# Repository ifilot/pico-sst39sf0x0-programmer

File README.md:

# PICO-SST39SF0x0 Programmer

> [!NOTE]  
> Wish to buy an assembled device? Feel free to contact me at ivo@ivofilot.nl. Price will be around €20,00. Will ship from the Netherlands.

> [!TIP]
> There also exists [a command-line tool](https://github.com/ifilot/pico-flasher-cli) to interface with the PICO-SST39SF0x0 Programmer.

> [!CAUTION]  
> Whenever possible, avoid using USB hubs to connect your **PICO-SST39SF0x0 Programmer**. 
> USB hubs can sometimes cause instability in the serial connection, which may 
> lead to crashes or unexpected program behavior.

## Obtaining pre-built binaries

Download the latest version of the binaries via the links below.

* [Firmware PICO (.uf2 file)](https://github.com/ifilot/pico-sst39sf0x0-programmer/releases/latest/download/pico-sst39sf0x0-programmer-firmware.uf2)
* [Firmware PICO2 (.uf2 file)](https://github.com/ifilot/pico-sst39sf0x0-programmer/releases/latest/download/pico2-sst39sf0x0-programmer-firmware.uf2)
* [GUI Installer](https://github.com/ifilot/pico-sst39sf0x0-programmer/releases/latest/download/pico-sst39sf0x0-programmer-installer-win64.exe)

## Purpose

This open hardware project aims users to produce a low-cost flasher for the
[SST39SF0x0 type](https://ww1.microchip.com/downloads/en/DeviceDoc/20005022C.pdf) 
of ROM chips. The flasher revolves around the cheap
[Raspberry PICO](https://www.raspberrypi.com/products/raspberry-pi-pico/) device.

Besides general read/write/erase functionality for the SST39SF0x0 type of ROM
chips, the software and tools delivered with the PICO-SST39SF0x0 Programmer tend
to cater to a number of projects involving the venerable 
[P2000T and P2000M](https://en.wikipedia.org/wiki/Philips_P2000), both early 
Philips home computers of the 1980s. See the list below for the projects that
use the PICO-SST39SF0x0 Programmer flasher.

* [P2000T Cartridges](https://github.com/ifilot/p2000t-cartridges): A set of
  homebrew cartridges designed for the P2000T. These cartridges all use
  SST39SF0x0 type of ROM chips.
* C64 Multirom

Nevertheless, this is a general purpose product and you are able to flash and
kind of data onto the ROM chips.

> [!TIP]  
> If you do not like seeing these ROM files being displayed, you can hide them
> via `Edit > Settings`.

## Device

The fully assembled device will look as seen in the image below. A ZIF-style
socket is used to insert the SST39SF0x0 chip. A reset button button is exposed
which will reset the device. The green and red LEDs will be on during read and
write operations, respectively. At the top-right part of the device, an access
hole is made to insert a long thin wire to press on the `bootsel` button of the
Raspberry Pi PICO. When this button is pressed down and a USB cable is inserted,
the PICO will expose a file system allowing the user to upload the firmware
to the device.

Inside the enclosure is a single PCB that hosts the PICO, the ZIF cartridge
and a number of chips. Since the GPIO pins on the PICO are 3.3V, extensive use
of level shifters is made to hook up the PICO to the SST39SF0x0 chip, whose
pins operate at the 5V logic level. To set the address on the SST39SF0x0 chip,
three 74HC573 chips are being used (U2-U4). A diode (D1) acts as the reverse
polarity protection in the event the user would place the chip in the wrong
direction.

PCB frontside | PCB backside
------------- | ------------
 | 

## GUI

To interface with the device, a GUI is written using the 
[Qt framework](https://www.qt.io/). The GUI scans for all USB devices connected
to the computer with a hardware signature matching the Raspberry Pi PICO. Upon
a match, it tries to access the device. Interfacing with the device occurs via
a [serial communication (COM) port](https://en.wikipedia.org/wiki/COM_(hardware_interface)).
By means of a number of [simple 8-byte command words](firmware/README.md),
instructions can be sent to the device and the corresponding response can be
received. One is not restricted to using the GUI to interface with the device.
An [example set of Python scripts](firmware/scripts) is provided to provide 
an alternative way to communicate with the PICO programmer.

> [!NOTE]  
> There is also a command-line tool available via
> [this repository](https://github.com/ifilot/pico-flasher-cli).

## Documentation and tutorials

A number of useful tutorials to work with the PICO programmer are provided
below.

* [Flashing the device / updating firmware](https://www.philips-p2000t.nl/tools/pico-sst39sf0x0-programmer.html#flashing-firmware-to-the-programmer)
* [Using the programmer to create copies of P2000T cartridges](https://www.philips-p2000t.nl/tools/pico-sst39sf0x0-programmer-slot1-adapter-board.html)
* [Using the PICO programmer in combination with the P2000T ZIF-cartridge](https://www.philips-p2000t.nl/cartridges/zif-cartridge.html#zif-cartridge)

## Schematics

[Download schematics as PDF](pcb/pico-sst39sf0x0-pcb/pico-sst39sf0x0-pcb.pdf)

## Contents

* [Case](case): Set of .stl files to print a handy case for your flash device.
* [Firmware](firmware): Firmware for your PICO to interface with the GUI.
* [GUI](gui): Qt-based GUI to interface with your PICO.
* [PCB](pcb): Kicad files to produce the PICO flash device and the PLCC32 adapter board.
* [Scripts](scripts): Number of Python scripts the correct working of your PICO
  device.

## License

* All software is shared under the [GPL v3 license](https://www.gnu.org/licenses/gpl-3.0).
* All hardware (e.g. KiCAD files and .stl files) are shared under the [CC-BY-SA 4.0 license](https://creativecommons.org/licenses/by-sa/4.0/).

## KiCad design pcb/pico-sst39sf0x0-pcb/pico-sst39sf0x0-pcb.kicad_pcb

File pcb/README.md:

# PCBs

This folder contains three subfolders containing the KiCAD files for three
PCBs

* [pico-sst39sf0x0-pcb](pico-sst39sf0x0-pcb): Core PCB containing the Raspberry
  Pi PICO, the ZIF socket and the required interfacing circuitry.
* [p2000t-slot1-adapter-board](p2000t-slot1-adapter-board): Adapter board for
  non-invasive extraction of data from SLOT1 cartridges for the P2000T
* [plcc32-adapter-board](plcc32-adapter-board): Adapter board for interfacing
  the DIP32 SST39SF0x0 chips with the PLCC32 variant.

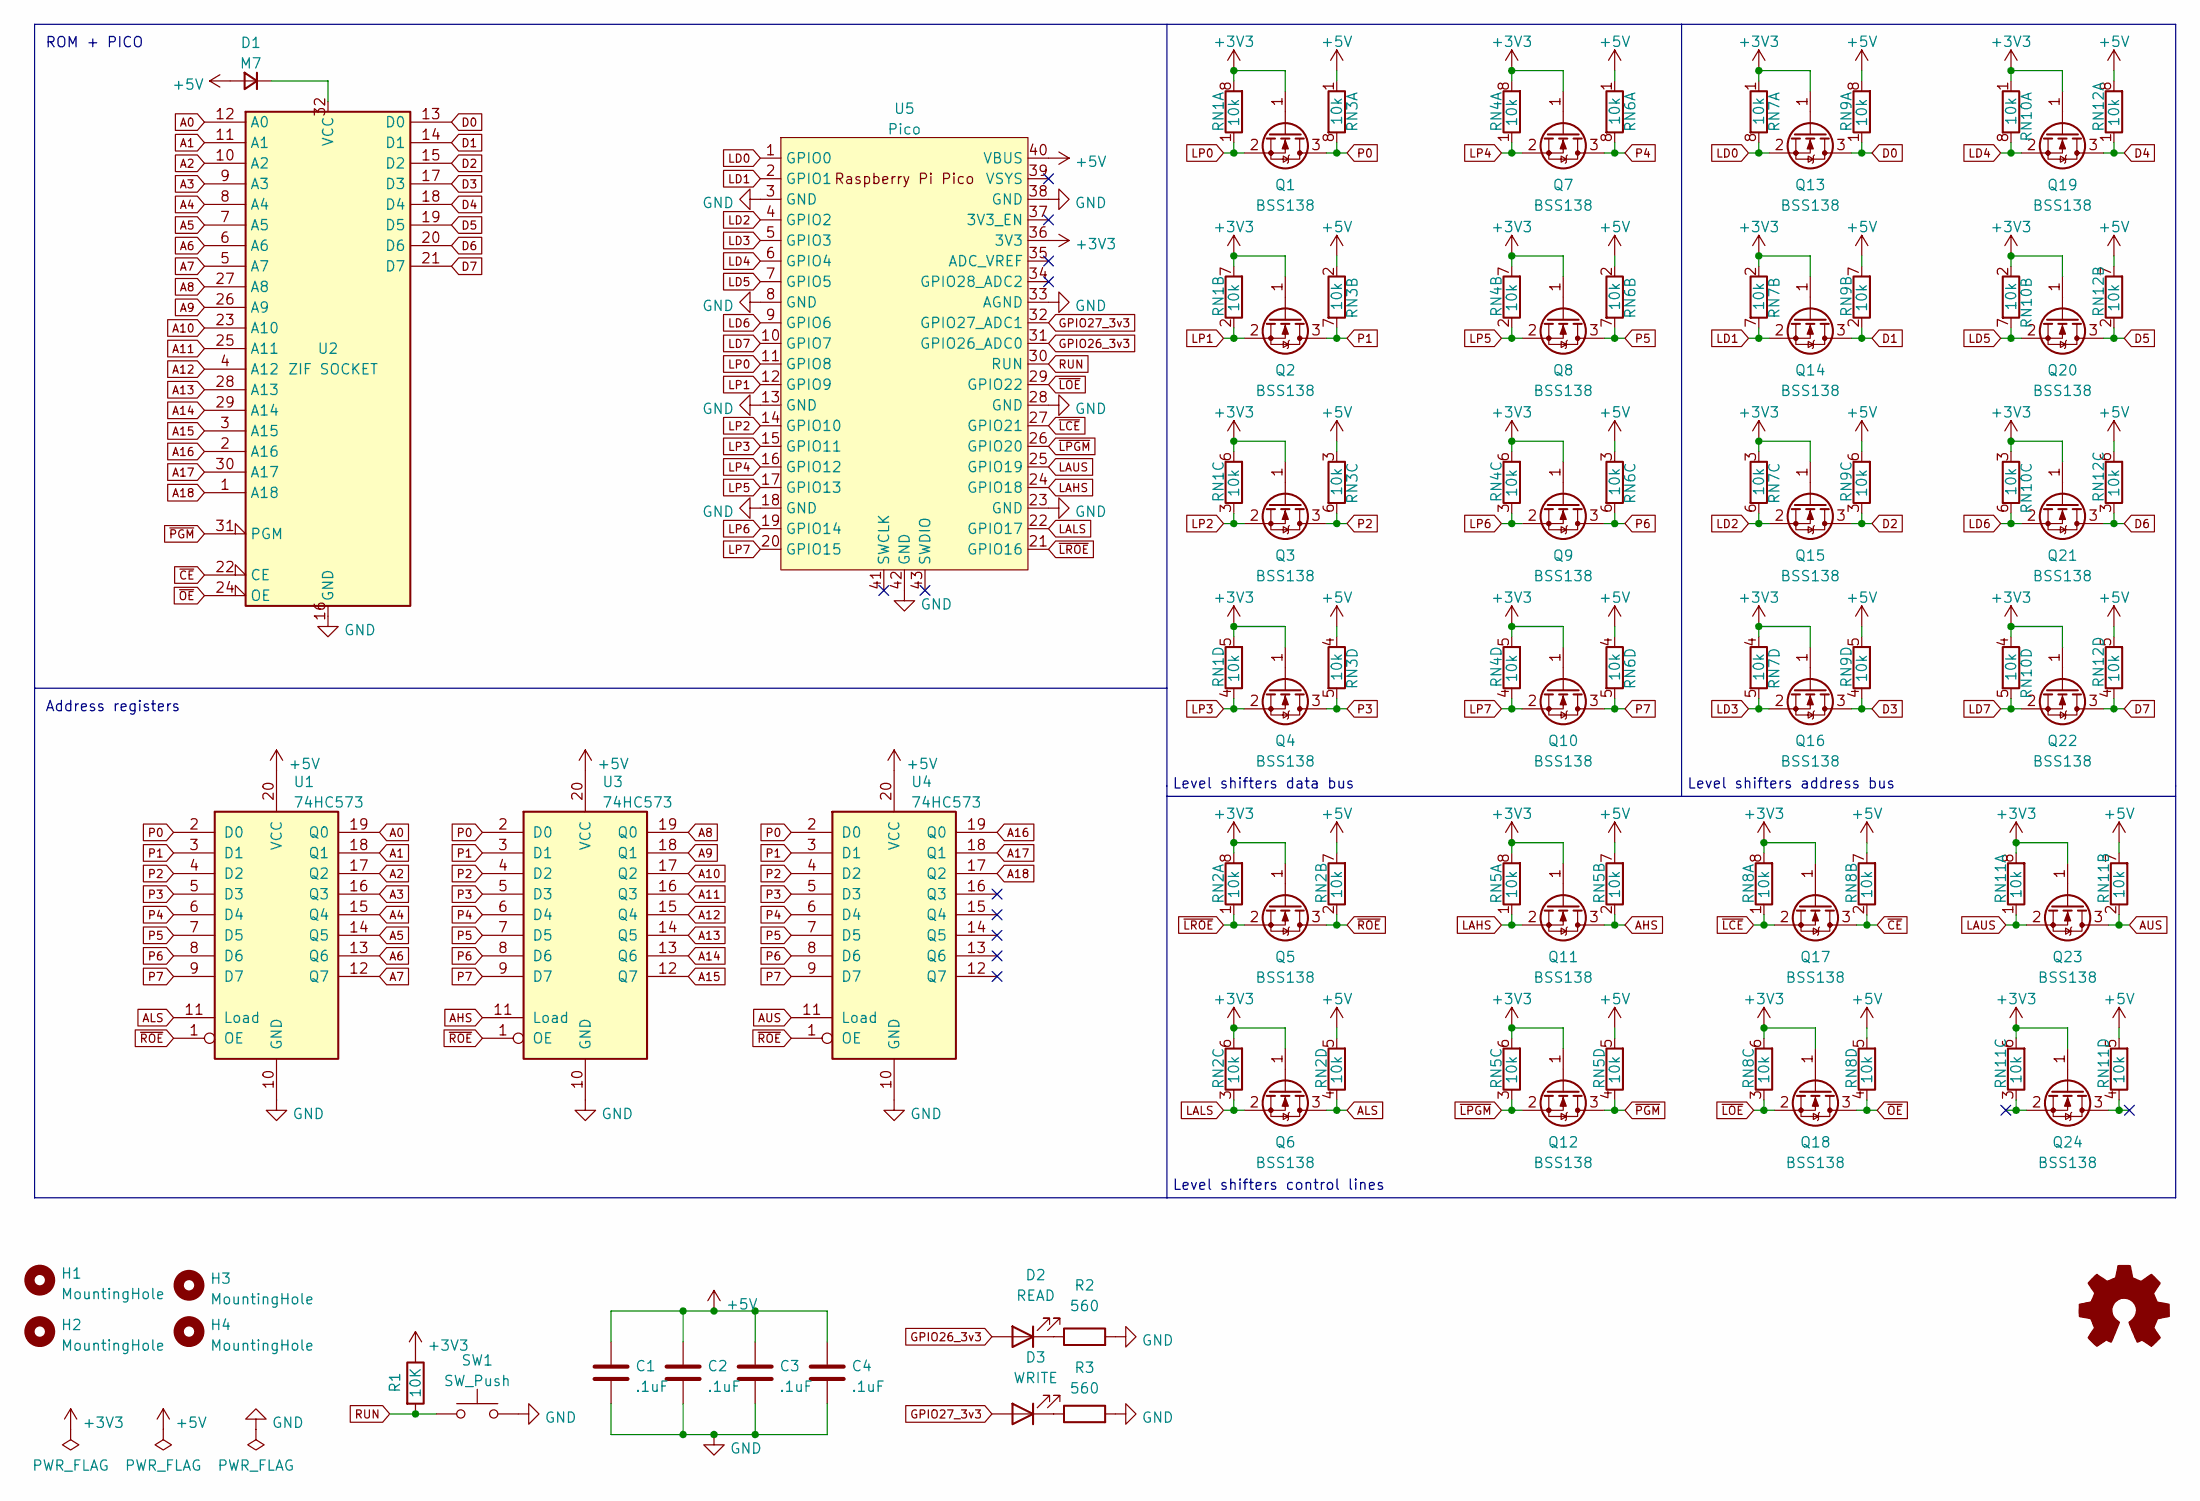
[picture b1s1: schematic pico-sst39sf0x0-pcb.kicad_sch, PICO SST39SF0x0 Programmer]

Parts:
C1, C2, C3, C4: .1uF; C_0805_2012Metric; LCSC C1790
D1: M7; D_SMA; LCSC C95872
D2: READ; LED_D5.0mm
D3: WRITE; LED_D5.0mm
G1: Logo_Open_Hardware_Small; OSHW-Logo_11.4x12mm_SilkScreen
H1, H2, H3, H4: MountingHole; MountingHole_3.2mm_M3
Q1, Q2, Q3, Q4, Q5, Q6, Q7, Q8, Q9, Q10, Q11, Q12, Q13, Q14, Q15, Q16, Q17, Q18, Q19, Q20, Q21, Q22, Q23, Q24: BSS138; SOT-23; LCSC C78284
R1: 10K; R_0805_2012Metric_Pad1.20x1.40mm_HandSolder; LCSC C17414
R2, R3: 560; R_0805_2012Metric_Pad1.20x1.40mm_HandSolder; LCSC C28636
RN1, RN2, RN3, RN4, RN5, RN6, RN7, RN8, RN9, RN10, RN11, RN12: 10k; R_Array_Convex_4x0603; LCSC C110924
SW1: SW_Push; SW_PUSH_6mm
U1, U3, U4: 74HC573; SOIC-20W_7.5x12.8mm_P1.27mm; LCSC C5608
U2: ZIF SOCKET; DIP_Socket-32_W11.9_W12.7_W15.24_W17.78_W18.5_3M_232-1285-0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
U5: Pico; RPi_Pico_SMD_TH

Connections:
+3V3: Q1.1 (G), Q2.1 (G), Q3.1 (G), Q4.1 (G), Q5.1 (G), Q6.1 (G), Q7.1 (G), Q8.1 (G), Q9.1 (G), Q10.1 (G), Q11.1 (G), Q12.1 (G), Q13.1 (G), Q14.1 (G), Q15.1 (G), Q16.1 (G), Q17.1 (G), Q18.1 (G), Q19.1 (G), Q20.1 (G), Q21.1 (G), Q22.1 (G), Q23.1 (G), Q24.1 (G), R1.1, RN1.5 (R4.2), RN1.6 (R3.2), RN1.7 (R2.2), RN1.8 (R1.2), RN2.6 (R3.2), RN2.8 (R1.2), RN4.5 (R4.2), RN4.6 (R3.2), RN4.7 (R2.2), RN4.8 (R1.2), RN5.6 (R3.2), RN5.8 (R1.2), RN7.1 (R1.1), RN7.2 (R2.1), RN7.3 (R3.1), RN7.4 (R4.1), RN8.6 (R3.2), RN8.8 (R1.2), RN10.1 (R1.1), RN10.2 (R2.1), RN10.3 (R3.1), RN10.4 (R4.1), RN11.6 (R3.2), RN11.8 (R1.2), U5.36 (3V3)
+5V: C1.1, C2.1, C3.1, C4.1, D1.2 (A), RN2.5 (R4.2), RN2.7 (R2.2), RN3.1 (R1.1), RN3.2 (R2.1), RN3.3 (R3.1), RN3.4 (R4.1), RN5.5 (R4.2), RN5.7 (R2.2), RN6.1 (R1.1), RN6.2 (R2.1), RN6.3 (R3.1), RN6.4 (R4.1), RN8.5 (R4.2), RN8.7 (R2.2), RN9.5 (R4.2), RN9.6 (R3.2), RN9.7 (R2.2), RN9.8 (R1.2), RN11.5 (R4.2), RN11.7 (R2.2), RN12.5 (R4.2), RN12.6 (R3.2), RN12.7 (R2.2), RN12.8 (R1.2), U1.20 (VCC), U3.20 (VCC), U4.20 (VCC), U5.40 (VBUS)
A0: U1.19 (Q0), U2.12 (A0)
A1: U1.18 (Q1), U2.11 (A1)
A2: U1.17 (Q2), U2.10 (A2)
A3: U1.16 (Q3), U2.9 (A3)
A4: U1.15 (Q4), U2.8 (A4)
A5: U1.14 (Q5), U2.7 (A5)
A6: U1.13 (Q6), U2.6 (A6)
A7: U1.12 (Q7), U2.5 (A7)
A8: U2.27 (A8), U3.19 (Q0)
A9: U2.26 (A9), U3.18 (Q1)
A10: U2.23 (A10), U3.17 (Q2)
A11: U2.25 (A11), U3.16 (Q3)
A12: U2.4 (A12), U3.15 (Q4)
A13: U2.28 (A13), U3.14 (Q5)
A14: U2.29 (A14), U3.13 (Q6)
A15: U2.3 (A15), U3.12 (Q7)
A16: U2.2 (A16), U4.19 (Q0)
A17: U2.30 (A17), U4.18 (Q1)
A18: U2.1 (A18), U4.17 (Q2)
AHS: Q11.3 (D), RN5.2 (R2.1), U3.11 (Load)
ALS: Q6.3 (D), RN2.4 (R4.1), U1.11 (Load)
AUS: Q23.3 (D), RN11.2 (R2.1), U4.11 (Load)
D0: Q13.3 (D), RN9.1 (R1.1), U2.13 (D0)
D1: Q14.3 (D), RN9.2 (R2.1), U2.14 (D1)
D2: Q15.3 (D), RN9.3 (R3.1), U2.15 (D2)
D3: Q16.3 (D), RN9.4 (R4.1), U2.17 (D3)
D4: Q19.3 (D), RN12.1 (R1.1), U2.18 (D4)
D5: Q20.3 (D), RN12.2 (R2.1), U2.19 (D5)
D6: Q21.3 (D), RN12.3 (R3.1), U2.20 (D6)
D7: Q22.3 (D), RN12.4 (R4.1), U2.21 (D7)
GND: C1.2, C2.2, C3.2, C4.2, R2.2, R3.2, SW1.2, U1.10 (GND), U2.16 (GND), U3.10 (GND), U4.10 (GND), U5.3 (GND), U5.8 (GND), U5.13 (GND), U5.18 (GND), U5.23 (GND), U5.28 (GND), U5.33 (AGND), U5.38 (GND), U5.42 (GND)
GPIO26_3v3: D2.2 (A), U5.31 (GPIO26_ADC0)
GPIO27_3v3: D3.2 (A), U5.32 (GPIO27_ADC1)
LAHS: Q11.2 (S), RN5.1 (R1.1), U5.24 (GPIO18)
LALS: Q6.2 (S), RN2.3 (R3.1), U5.22 (GPIO17)
LAUS: Q23.2 (S), RN11.1 (R1.1), U5.25 (GPIO19)
LD0: Q13.2 (S), RN7.8 (R1.2), U5.1 (GPIO0)
LD1: Q14.2 (S), RN7.7 (R2.2), U5.2 (GPIO1)
LD2: Q15.2 (S), RN7.6 (R3.2), U5.4 (GPIO2)
LD3: Q16.2 (S), RN7.5 (R4.2), U5.5 (GPIO3)
LD4: Q19.2 (S), RN10.8 (R1.2), U5.6 (GPIO4)
LD5: Q20.2 (S), RN10.7 (R2.2), U5.7 (GPIO5)
LD6: Q21.2 (S), RN10.6 (R3.2), U5.9 (GPIO6)
LD7: Q22.2 (S), RN10.5 (R4.2), U5.10 (GPIO7)
LP0: Q1.2 (S), RN1.1 (R1.1), U5.11 (GPIO8)
LP1: Q2.2 (S), RN1.2 (R2.1), U5.12 (GPIO9)
LP2: Q3.2 (S), RN1.3 (R3.1), U5.14 (GPIO10)
LP3: Q4.2 (S), RN1.4 (R4.1), U5.15 (GPIO11)
LP4: Q7.2 (S), RN4.1 (R1.1), U5.16 (GPIO12)
LP5: Q8.2 (S), RN4.2 (R2.1), U5.17 (GPIO13)
LP6: Q9.2 (S), RN4.3 (R3.1), U5.19 (GPIO14)
LP7: Q10.2 (S), RN4.4 (R4.1), U5.20 (GPIO15)
unnamed: D1.1 (K), U2.32 (VCC)
unnamed: D2.1 (K), R2.1
unnamed: D3.1 (K), R3.1
P0: Q1.3 (D), RN3.8 (R1.2), U1.2 (D0), U3.2 (D0), U4.2 (D0)
P1: Q2.3 (D), RN3.7 (R2.2), U1.3 (D1), U3.3 (D1), U4.3 (D1)
P2: Q3.3 (D), RN3.6 (R3.2), U1.4 (D2), U3.4 (D2), U4.4 (D2)
P3: Q4.3 (D), RN3.5 (R4.2), U1.5 (D3), U3.5 (D3), U4.5 (D3)
P4: Q7.3 (D), RN6.8 (R1.2), U1.6 (D4), U3.6 (D4), U4.6 (D4)
P5: Q8.3 (D), RN6.7 (R2.2), U1.7 (D5), U3.7 (D5), U4.7 (D5)
P6: Q9.3 (D), RN6.6 (R3.2), U1.8 (D6), U3.8 (D6), U4.8 (D6)
P7: Q10.3 (D), RN6.5 (R4.2), U1.9 (D7), U3.9 (D7), U4.9 (D7)
RUN: R1.2, SW1.1, U5.30 (RUN)
~CE: Q17.3 (D), RN8.2 (R2.1), U2.22 (CE)
~LCE: Q17.2 (S), RN8.1 (R1.1), U5.27 (GPIO21)
~LOE: Q18.2 (S), RN8.3 (R3.1), U5.29 (GPIO22)
~LPGM: Q12.2 (S), RN5.3 (R3.1), U5.26 (GPIO20)
~LROE: Q5.2 (S), RN2.1 (R1.1), U5.21 (GPIO16)
~OE: Q18.3 (D), RN8.4 (R4.1), U2.24 (OE)
~PGM: Q12.3 (D), RN5.4 (R4.1), U2.31 (PGM)
~ROE: Q5.3 (D), RN2.2 (R2.1), U1.1 (OE), U3.1 (OE), U4.1 (OE)

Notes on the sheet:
Level shifters control lines
Level shifters data bus
Level shifters address bus
ROM + PICO
Address registers

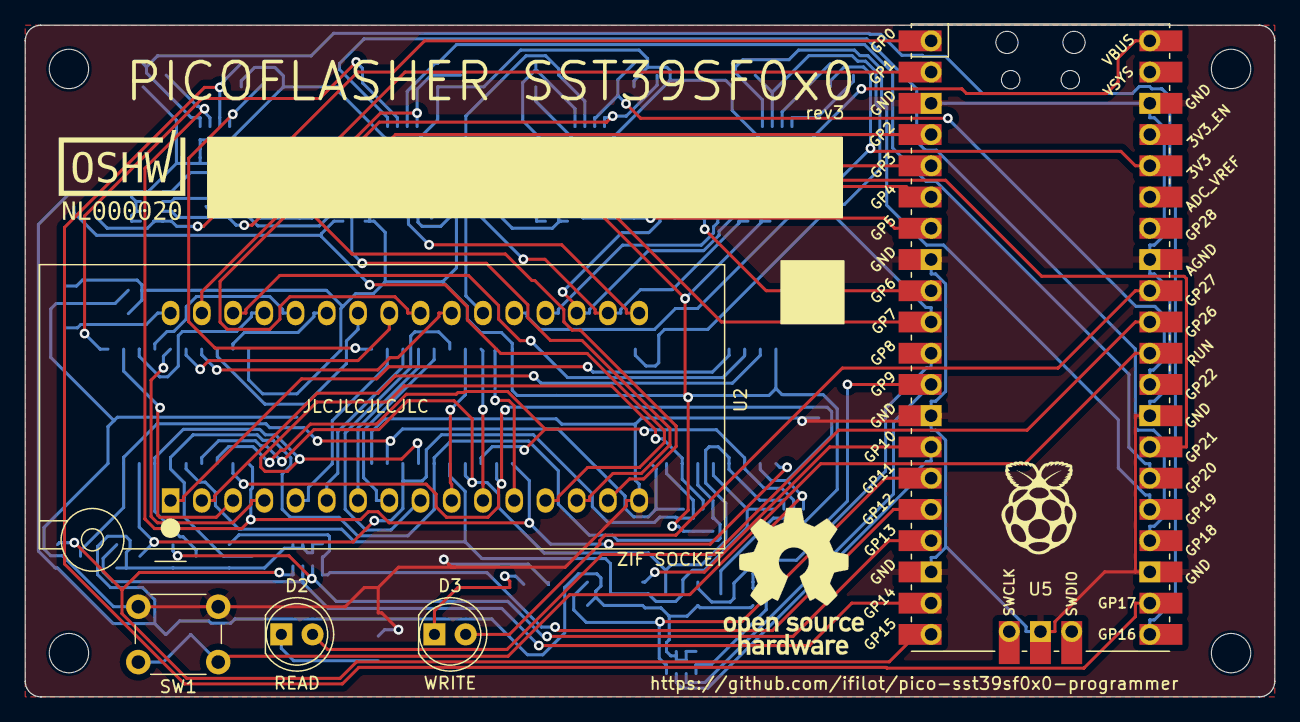
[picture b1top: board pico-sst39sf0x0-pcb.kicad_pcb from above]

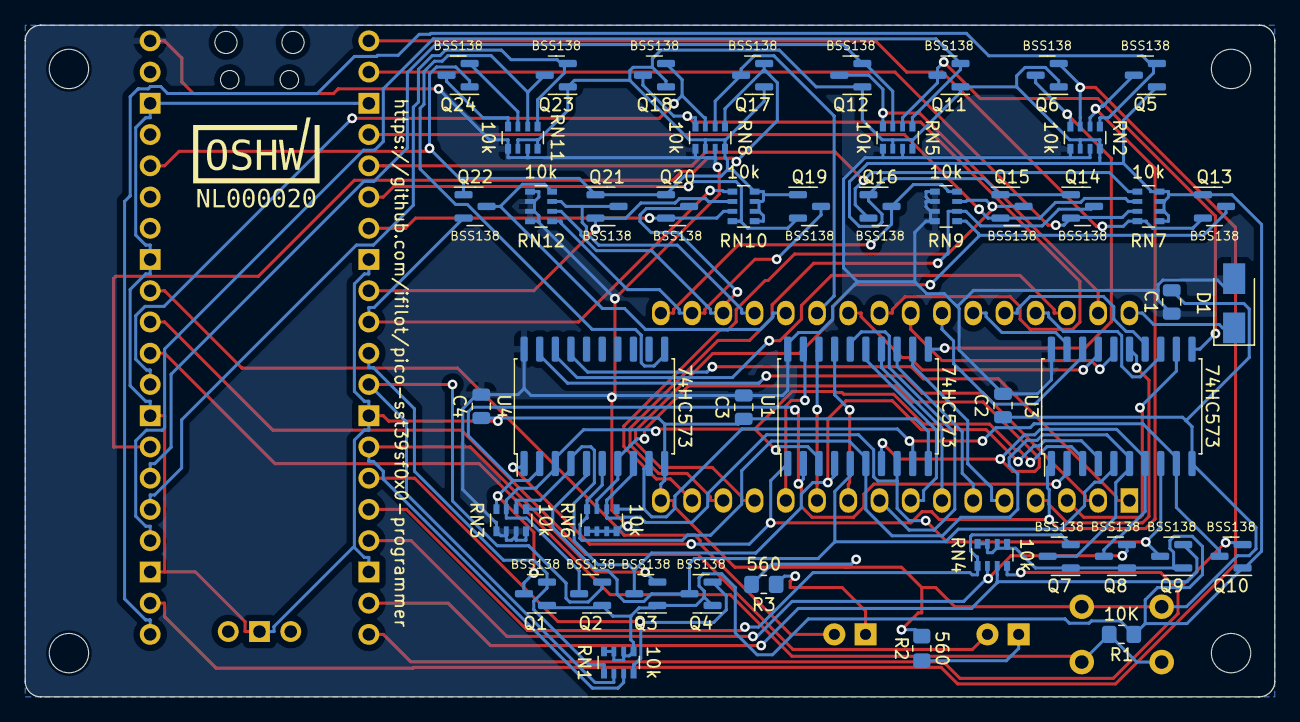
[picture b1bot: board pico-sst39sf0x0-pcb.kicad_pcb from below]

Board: 2 copper layers, 101.6 x 54.6 mm, 60 parts (48 on the bottom side), 74 nets.

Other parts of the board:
G1#2: Logo_Open_Hardware_Small; OSHW-Logo_11.4x12mm_SilkScreen
G1#3: LOGO; oshw_certificate_stacked
G4: LOGO; raspberry_pi_logo

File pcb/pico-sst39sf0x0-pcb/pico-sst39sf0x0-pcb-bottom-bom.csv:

Comment,Designator,Footprint,LCSC Part #
.1uF Unpolarized capacitor,"C1,C2,C3,C4",C_0805_2012Metric,C1790
"M7 Diode, small symbol",D1,D_SMA,C95872
"BSS138 50V Vds, 0.22A Id, N-Channel MOSFET, SOT-23","Q1,Q2,Q3,Q4,Q5,Q6,Q7,Q8,Q9,Q10,Q11,Q12,Q13,Q14,Q15,Q16,Q17,Q18,Q19,Q20,Q21,Q22,Q23,Q24",SOT-23,C78284
10K Resistor,R1,R_0805_2012Metric_Pad1.20x1.40mm_HandSolder,C17414
560 Resistor,"R2,R3",R_0805_2012Metric_Pad1.20x1.40mm_HandSolder,C28636
"10k 4 resistor network, parallel topology, split","RN1,RN2,RN3,RN4,RN5,RN6,RN7,RN8,RN9,RN10,RN11,RN12",R_Array_Convex_4x0603,C110924
74HC573 8-bit Latch 3-state outputs,"U1,U3,U4",SOIC-20W_7.5x12.8mm_P1.27mm,C5608

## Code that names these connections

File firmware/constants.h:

/****************************************************************************
 *                                                                          *
 *   PICO-SST39SF0x0-FLASHER-FIRMWARE                                       *
 *   Copyright (C) 2023 Ivo Filot <ivo@ivofilot.nl>                         *
 *                                                                          *
 *   This program is free software: you can redistribute it and/or modify   *
 *   it under the terms of the GNU Lesser General Public License as         *
 *   published by the Free Software Foundation, either version 3 of the     *
 *   License, or (at your option) any later version.                        *
 *                                                                          *
 *   This program is distributed in the hope that it will be useful,        *
 *   but WITHOUT ANY WARRANTY; without even the implied warranty of         *
 *   MERCHANTABILITY or FITNESS FOR A PARTICULAR PURPOSE.  See the          *
 *   GNU General Public License for more details.                           *
 *                                                                          *
 *   You should have received a copy of the GNU General Public license      *
 *   along with this program.  If not, see <https://www.gnu.org/licenses/>. *
 *                                                                          *
 ****************************************************************************/

#ifndef _CONSTANTS_H
#define _CONSTANTS_H

/*
There is one 8-bit bus that is used to set the address registers. This
8-bit bus corresponds to GPIO8 - GPIO15.

GPIO16 - OE of all address registers
GPIO17 - LOAD for A0-A7
GPIO18 - LOAD for A8-A15
GPIO19 - LOAD for A16-A19
*/

#define ROE 16
#define ALS 17
#define AHS 18
#define AUS 19
#define PGM 20
#define CE  21
#define OE  22
#define LED_RD 26
#define LED_WR 27

#define DELAY_READ 3
#define DELAY_READ_VERIFY 1
#define DELAY_WRITE 1
#define DELAY_ADDR 1
#define BOARD_ID "PICOSST39-v1.6.0"

#define BLOCK_SIZE  0x100
#define SECTOR_SIZE 0x1000
#define BANK_SIZE   0x4000

#define NOP __asm volatile ("nop\n");
#define NOP50 __asm volatile ("nop\nnop\nnop\nnop\nnop\nnop\nnop\nnop\nnop\nnop\nnop\nnop\nnop\nnop\nnop\nnop\nnop\nnop\nnop\nnop\nnop\nnop\nnop\nnop\nnop\nnop\nnop\nnop\nnop\nnop\nnop\nnop\nnop\nnop\nnop\nnop\nnop\nnop\nnop\nnop\nnop\nnop\nnop\nnop\nnop\nnop\nnop\nnop\nnop\nnop\n");

#endif

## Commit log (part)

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2023-08-07 Adding PCB images
2023-08-08 Adding LEDs and putting 10k resistor on backside
2023-08-23 Adding adapter board for p2000t-slot1 cartridges
2023-08-23 Adding polarity protection diode and 10k resistor on backside. Adding LEDS on front side
2023-09-02 Expanding firmware and GUI to accept P2000T adapter cartridge
2023-09-02 Revising P2000T adapter board to accomodate ZIF lever
2023-09-02 Adding README files
2023-09-06 Adding LEDs
2023-09-08 Adding LEDs to the firmware
2023-09-08 Pcbrev1 (#1)
    * Adding LEDs and putting 10k resistor on backside
    * Adding polarity protection diode and 10k resistor on backside. Adding LEDS on front side
    * Adding LEDs
    * Adding LEDs to the firmware
2023-09-08 Removing MacOS support
2023-09-08 Expanding documentation
2023-09-08 Pcbrev1 (#1) (#2)
    * Adding LEDs and putting 10k resistor on backside
    * Adding polarity protection diode and 10k resistor on backside. Adding LEDS on front side
    * Adding LEDs
    * Adding LEDs to the firmware
2023-09-08 Improving case
2023-09-14 Expanding README and improving case
2023-09-14 Expanding firmware and improving functionality of GUI
2023-09-17 Modifying adapter board
2023-09-17 Implementing sector based writing
2023-09-17 Changing function names for sectors
2023-09-17 Adding individual ROMS
2023-09-17 Expanding README.md and reorganizing commands
2023-09-17 Adding helloworld
2023-09-17 Adding functionality (#3)
    * Adding adapter board for p2000t-slot1 cartridges
    * Expanding firmware and GUI to accept P2000T adapter cartridge
    * Revising P2000T adapter board to accomodate ZIF lever
    * Adding README files
    * Removing MacOS support
    * Expanding documentation
2023-09-21 Fixing a few bugs and adding data information
2023-09-21 Fixing badge README
2023-09-21 Patch 1.1.1 (#4)
    * Fixing a few bugs and adding data information
    * Fixing badge README
2023-09-21 Fixing deployment file
2023-09-23 Adding version number in GUI and adjusting menu options for different types of SST39SF0x0 chips
2023-09-23 Adding version number in GUI and adjusting menu options for different types of SST39SF0x0 chips (#5)
2023-09-24 Improving case and fixing bug in GUI
2023-09-24 Improving case and fixing bug in GUI (#6)
2023-10-11 Fixing instructions for Ubuntu
2023-10-15 Expanding on documentation
2023-10-15 Expanding documentation (#7)
    * Fixing instructions for Ubuntu
    * Expanding on documentation
2023-10-15 Adding debug log and better exception management
2023-10-15 Adding missing files to CMakeList.txt
2023-10-15 Adding header
2023-10-15 Adding debug log and better exception management (#8)
    * Adding debug log and better exception management
    * Adding missing files to CMakeList.txt
    * Adding header
2023-11-12 Adding button to completely erase a chip
2023-11-12 Expanding README.md
2023-11-12 Updating release version and date
2023-11-12 Patch 1.3.0 (#9)
    * Adding button to completely erase a chip
    * Expanding README.md
2023-11-12 Fixing bug in board id recognition
2024-03-08 Initial commit revision 2
2024-03-19 Revising top case
2024-04-03 Changing license conditions in README.md
2024-04-03 Fixing typos
2024-04-03 Adding badge
2024-04-03 Updating README files
2024-04-03 Updating installer version
2024-04-03 Updating photo
2024-04-03 Updating photos PCBs
2024-04-03 Revision 2 of the PCB (#11)
    * Initial commit revision 2
    * Revising top case
    * Updating photo
    * Updating photos PCBs
2024-04-06 Tweaking lay-out PCB
2024-04-12 Initial commit TinyUSB interface
2024-04-12 Improving speed of read and write routines
2024-04-13 Adding switch for P2K edition
2024-04-13 Initial commit Settings object
2024-04-13 Adding settings widget
2024-04-13 Refactoring hexviewer
2024-04-13 Removing events
2024-04-13 Templated installer
2024-04-13 Tackling issue #10
2024-04-13 Fixing templated deployment
2024-04-13 Adding OSHW image
2024-04-13 Set colors via settings menu
2024-04-13 Implementing color themes
2024-04-14 Storing last file paths
2024-04-14 Adding more color schemes
2024-04-14 Setting custom font
2024-04-14 Setting MD5sum as uppercase
2024-04-14 Adding another color scheme
2024-04-14 Tuning firmware and GUI
2024-04-14 Fixing bug in read sector
2024-04-14 Fixing bug in dialog selection
2024-04-21 Upgrading actions to Qt 6.7.0
2024-04-21 Upgrading to Qt6 in CMakeLists.txt
2024-04-21 Adding qtserialport module
2024-04-21 Expanding libraries
2024-04-21 Adding missing file
2024-04-21 Adding serialport module
2024-04-21 Adding OpenSSLv3
2024-04-21 Adding more ROMS and fixing function in SettingsWidget class
2024-04-21 Tuning font size
2024-04-21 Version 1.4.0 (#12)
    * Initial commit TinyUSB interface
    * Improving speed of read and write routines
    * Adding switch for P2K edition
    * Initial commit Settings object
    * Adding settings widget
    * Refactoring hexviewer
2024-04-21 Adding bank viewer
2024-04-21 Changing type
2024-04-21 Version 1.5.0 (#13)
    * Adding bank viewer
    * Changing type
2024-04-21 Adding schematics
2024-04-24 Fixing bugs
2024-04-24 Fixing bugs (#15)
2024-05-01 Improving error messages
2024-05-01 Incrementing version for firmware to match GUI
2024-05-01 Patch v1.5.2 (#16)
    * Improving error messages
    * Incrementing version for firmware to match GUI
2024-06-14 Initial commit Refactoring installer
2024-06-22 Adding multimaterial case
2024-12-22 Adding support for PICO2
2024-12-22 Adding hardware ID for PICO2
2024-12-22 Changing versions
2024-12-22 Changing docker image
2024-12-22 Fixing version
2024-12-22 Changing platform
2024-12-22 Fixing docker image name
2024-12-22 Changing back name
2024-12-22 Removing ref
2024-12-22 Further removing references
2024-12-22 Updating README.md
2024-12-22 Patch 1.6.0: Support for Raspberry Pi PICO2 (#17)
    * Initial commit Refactoring installer
    * Adding multimaterial case
    * Adding support for PICO2
    * Adding hardware ID for PICO2
    * Changing versions
    * Changing docker image
2025-01-04 Adding case for 36mm inserts
2025-01-04 Updating lay-out
2025-01-13 Removing P2000T roms from repository and adding hyperlinks to download latest version from internet
2025-01-13 Removing P2000T roms from repository and adding hyperlinks to download latest version from internet (#18)
2025-01-14 Showing multimaterial case
2025-01-15 Adding P2000T ROM
2025-01-19 Initial try GA rendering
2025-02-21 Small adjustment to ROMs collection
2025-02-21 Updating GA script
2025-02-21 Patch v1.7.2 (#19)
    * Small adjustment to ROMs collection
    * Updating GA script
2025-06-05 Adding quickwrite functionality
2025-06-27 Modifying installer
2025-06-27 Adding installer icon
2025-06-29 Removing version from folder name
2025-06-29 Modifying templates
2025-07-02 Further tuning installer
2025-07-02 Changing launcher script and always using quickflash
2025-07-02 Adding line
2025-07-02 Yet another change
2025-07-02 Making another change
2025-07-03 Replacing installer
2025-07-03 Adjusting script
2025-07-03 Fixing reference
2025-07-03 Fixing link
2025-07-03 Fixing script
2025-07-04 Showing folder
2025-07-04 Doing tree
2025-07-04 Changing paths
2025-07-04 Ensuring same version
2025-07-04 New verison
2025-07-04 Back to 6.7.0
2025-07-04 Aligning toolchain
2025-07-04 Release 1.8.0 (#20)
    * Adding quickwrite functionality
    * Modifying installer
    * Adding installer icon
    * Removing version from folder name
    * Modifying templates
    * Further tuning installer
2025-07-04 Explicitly writing filenames
2025-07-04 List files before upload
2025-07-04 Changing file name
2026-02-06 Initial commit refactoring code
2026-02-06 Changing folder
2026-02-06 Fixing package
2026-02-06 Tuning installer
2026-02-06 Rewriting installer
2026-02-06 Rewriting variables
2026-02-06 Changing slash
2026-02-06 Fixing 302 error
2026-02-06 Fixing issue #21
2026-02-06 Patch v1.9.0 (#22)
    * Initial commit refactoring code
    * Changing folder
    * Fixing package
    * Tuning installer
    * Rewriting installer
    * Rewriting variables
2026-02-06 Fixing installer script
2026-02-06 Changing output file name
2026-02-06 Develop (#23)
    * Fixing installer script
    * Changing output file name
2026-02-08 Updating md5 checksums assuming cartridge size is strictly 16 KiB
2026-02-08 Updating md5 checksums assuming cartridge size is strictly 16 KiB (#24)
2026-04-11 Patching bugs in code
2026-04-12 Integrating test suite in work flow

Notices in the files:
README.md:
License: GPL v3
License: CC BY-SA 4.0
